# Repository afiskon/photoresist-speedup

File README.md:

# photoresist-speedup

Исходники к статье "Паяем таймер и матрицу из УФ-светодиодов для быстрой
засветки фоторезиста".

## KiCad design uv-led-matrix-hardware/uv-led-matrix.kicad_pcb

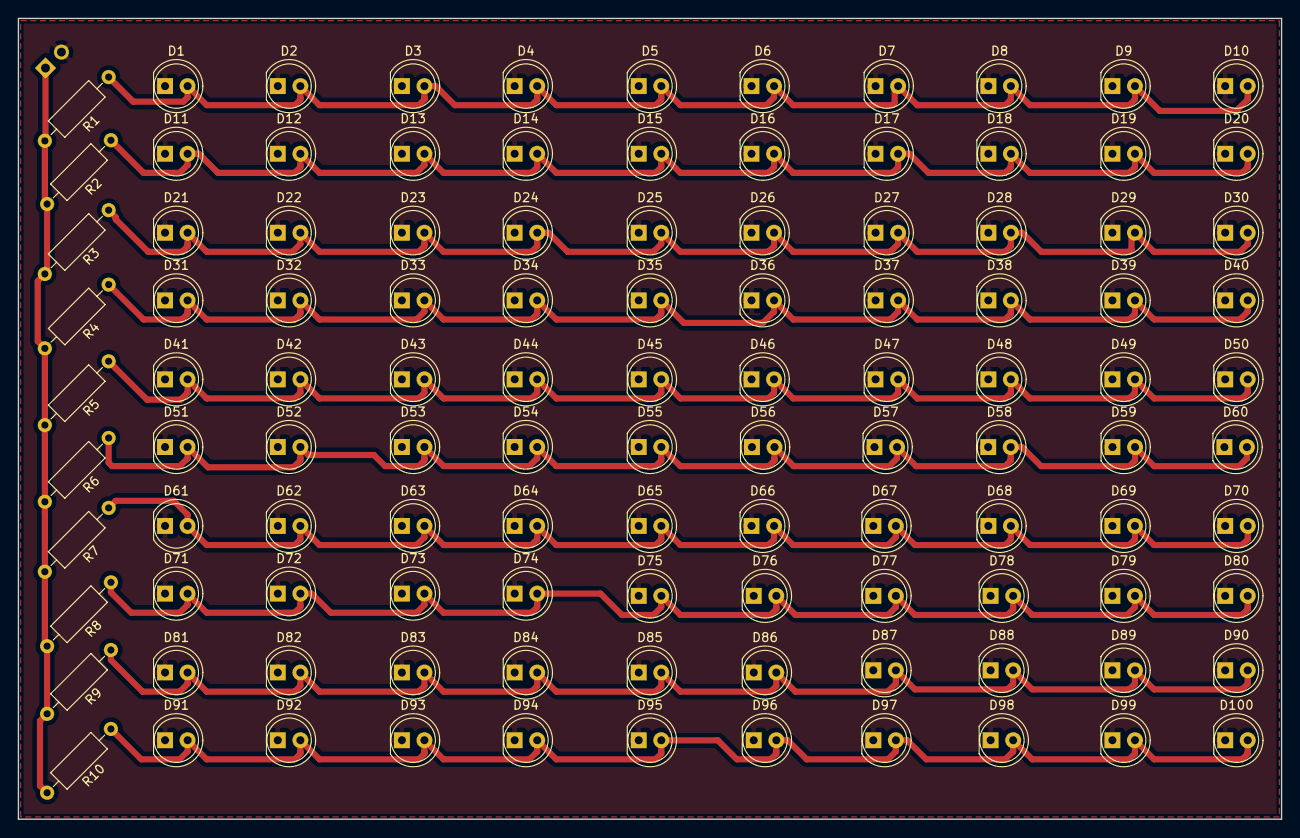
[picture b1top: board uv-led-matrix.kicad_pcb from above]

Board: 2 copper layers, 142.2 x 90.2 mm, 111 parts (1 on the bottom side), 12 nets.

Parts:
D1, D2, D3, D4, D5, D6, D7, D8, D9, D10, D11, D12, D13, D14, D15, D16, D17, D18, D19, D20, D21, D22, D23, D24, D25, D26, D27, D28, D29, D30, D31, D32, D33, D34, D35, D36, D37, D38, D39, D40, D41, D42, D43, D44, D45, D46, D47, D48, D49, D50, D51, D52, D53, D54, D55, D56, D57, D58, D59, D60, D61, D62, D63, D64, D65, D66, D67, D68, D69, D70, D71, D72, D73, D74, D75, D76, D77, D78, D79, D80, D81, D82, D83, D84, D85, D86, D87, D88, D89, D90, D91, D92, D93, D94, D95, D96, D97, D98, D99, D100: LED; LED_D5.0mm
J1: Conn_01x02; Pin_Header_Straight_1x02_Pitch2.54mm
R1, R2, R3, R4, R5, R6, R7, R8, R9, R10: 27; R_Axial_DIN0207_L6.3mm_D2.5mm_P10.16mm_Horizontal

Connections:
+5V: J1.1, R1.2, R2.2, R3.2, R4.2, R5.2, R6.2, R7.2, R8.2, R9.2, R10.2
GND: D1.1, D2.1, D3.1, D4.1, D5.1, D6.1, D7.1, D8.1, D9.1, D10.1, D11.1, D12.1, D13.1, D14.1, D15.1, D16.1, D17.1, D18.1, D19.1, D20.1, D21.1, D22.1, D23.1, D24.1, D25.1, D26.1, D27.1, D28.1, D29.1, D30.1, D31.1, D32.1, D33.1, D34.1, D35.1, D36.1, D37.1, D38.1, D39.1, D40.1, D41.1, D42.1, D43.1, D44.1, D45.1, D46.1, D47.1, D48.1, D49.1, D50.1, D51.1, D52.1, D53.1, D54.1, D55.1, D56.1, D57.1, D58.1, D59.1, D60.1, D61.1, D62.1, D63.1, D64.1, D65.1, D66.1, D67.1, D68.1, D69.1, D70.1, D71.1, D72.1, D73.1, D74.1, D75.1, D76.1, D77.1, D78.1, D79.1, D80.1, D81.1, D82.1, D83.1, D84.1, D85.1, D86.1, D87.1, D88.1, D89.1, D90.1, D91.1, D92.1, D93.1, D94.1, D95.1, D96.1, D97.1, D98.1, D99.1, D100.1, J1.2
unnamed: D1.2, D2.2, D3.2, D4.2, D5.2, D6.2, D7.2, D8.2, D9.2, D10.2, R1.1
unnamed: D11.2, D12.2, D13.2, D14.2, D15.2, D16.2, D17.2, D18.2, D19.2, D20.2, R2.1
unnamed: D21.2, D22.2, D23.2, D24.2, D25.2, D26.2, D27.2, D28.2, D29.2, D30.2, R3.1
unnamed: D31.2, D32.2, D33.2, D34.2, D35.2, D36.2, D37.2, D38.2, D39.2, D40.2, R4.1
unnamed: D41.2, D42.2, D43.2, D44.2, D45.2, D46.2, D47.2, D48.2, D49.2, D50.2, R5.1
unnamed: D51.2, D52.2, D53.2, D54.2, D55.2, D56.2, D57.2, D58.2, D59.2, D60.2, R6.1
unnamed: D61.2, D62.2, D63.2, D64.2, D65.2, D66.2, D67.2, D68.2, D69.2, D70.2, R7.1
unnamed: D71.2, D72.2, D73.2, D74.2, D75.2, D76.2, D77.2, D78.2, D79.2, D80.2, R8.1
unnamed: D81.2, D82.2, D83.2, D84.2, D85.2, D86.2, D87.2, D88.2, D89.2, D90.2, R9.1
unnamed: D91.2, D92.2, D93.2, D94.2, D95.2, D96.2, D97.2, D98.2, D99.2, D100.2, R10.1

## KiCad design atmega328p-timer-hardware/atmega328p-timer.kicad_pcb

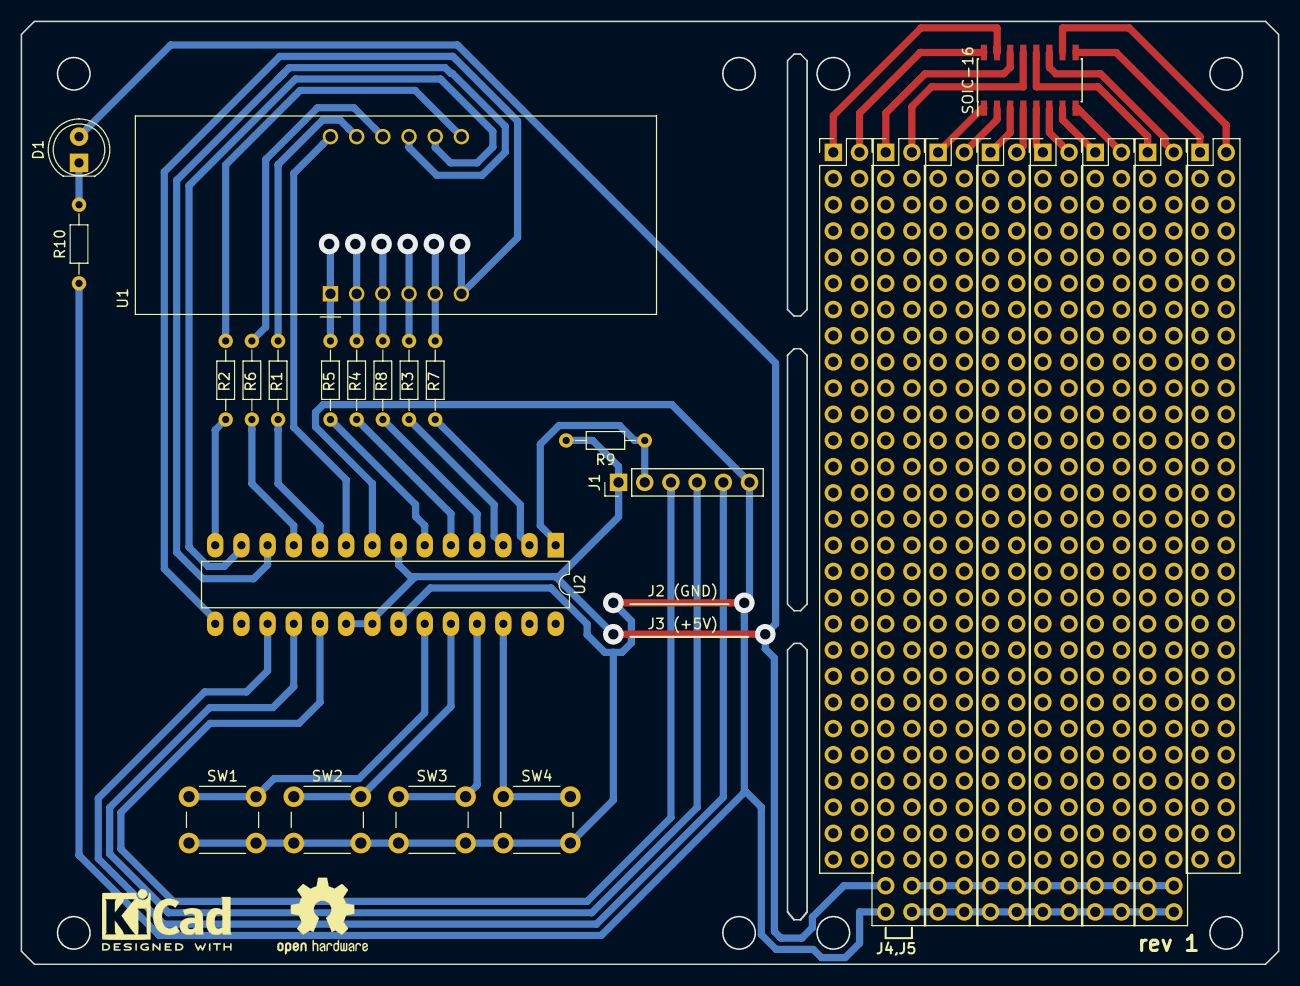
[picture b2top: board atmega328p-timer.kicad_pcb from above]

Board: 2 copper layers, 121.9 x 91.4 mm, 19 parts (0 on the bottom side), 31 nets.

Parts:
D1: LED; LED_D5.0mm
J1: Conn_01x06; Pin_Header_Straight_1x06_Pitch2.54mm
R1, R2, R3, R4, R5, R6, R7, R8, R10: 270; R_Axial_DIN0204_L3.6mm_D1.6mm_P7.62mm_Horizontal
R9: 10K; R_Axial_DIN0204_L3.6mm_D1.6mm_P7.62mm_Horizontal
SOIC-16: SOIC-16_3.9x9.9mm_Pitch1.27mm
SW1, SW2, SW3, SW4: SW_Push; SW_PUSH_6mm
U1: CA56-12CGKWA
U2: ATMEGA168A-PU; DIP-28_W7.62mm_LongPads

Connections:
+5V: D1.2, J1.1, R9.2, U2.7, U2.20, U2.21
GND: J1.6, R10.1, SW1.2, SW2.2, SW3.2, SW4.2, U2.8, U2.22
MISO: J1.4, U2.18
MOSI: J1.5, U2.17
unnamed: D1.1, R10.2
unnamed: R1.1, U1.11
unnamed: R2.1, U1.7
unnamed: R3.1, U1.4
unnamed: R4.1, U1.2
unnamed: R5.1, U1.1
unnamed: R6.1, U1.10
unnamed: R7.1, U1.5
unnamed: R8.1, U1.3
PB0: R2.2, U2.14
PB1: U1.6, U2.15
PB6: U1.12, U2.9
PB7: R1.2, U2.10
PC0: SW1.1, U2.23
PC1: SW2.1, U2.24
PC2: SW3.1, U2.25
PC3: SW4.1, U2.26
PD0: R7.2, U2.2
PD1: R3.2, U2.3
PD2: R8.2, U2.4
PD3: R4.2, U2.5
PD4: R5.2, U2.6
PD5: R6.2, U2.11
PD6: U1.9, U2.12
PD7: U1.8, U2.13
RESET: J1.2, R9.1, U2.1
SCK: J1.3, U2.19

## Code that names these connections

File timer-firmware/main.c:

/* vim: set ai et ts=4 sw=4: */

#define F_CPU 1000000

#include <avr/io.h>
#include <avr/eeprom.h>
#include <util/delay.h>
#include <string.h>
#include <stdbool.h>

void inc_time(int8_t* time) {
    for(uint8_t i = 0; i < 4; i++) {
        time[i]++;
        if(time[i] == 10) {
            // digit overflowed, go to the next one
            time[i] = 0;
        } else {
            // done!
            break;
        }
    }
}

void dec_time(int8_t* time) {
    for(uint8_t i = 0; i < 4; i++) {
        time[i]--;
        if(time[i] == -1) {
            // digit overflowed, go to the next one
            time[i] = 9;
        } else {
            // done!
            break;
        }
    }
}

bool time_is_zero(int8_t* time) {
    return (!time[0]) && (!time[1]) && (!time[2]) && (!time[3]);
}

void relay(bool on) {
    if(on) {
        PORTB |= (1 << 5);
    } else {
        PORTB &= ~(1 << 5);
    }
}

void seg_g(bool on) {
    if(on) {
        PORTD |= (1 << 0);
    } else {
        PORTD &= ~(1 << 0);
    }
}

void seg_c(bool on) {
    if(on) {
        PORTD |= (1 << 1);
    } else {
        PORTD &= ~(1 << 1);
    }
}

void seg_h(bool on) {
    if(on) {
        PORTD |= (1 << 2);
    } else {
        PORTD &= ~(1 << 2);
    }
}

void seg_d(bool on) {
    if(on) {
        PORTD |= (1 << 3);
    } else {
        PORTD &= ~(1 << 3);
    }
}

void seg_e(bool on) {
    if(on) {
        PORTD |= (1 << 4);
    } else {
        PORTD &= ~(1 << 4);
    }
}

void digit0(bool on) {
    // _low_ voltage enables the digit
    if(on) {
        PORTB &= ~(1 << 6);
    } else {
        PORTB |= (1 << 6);
    }
}

void seg_a(bool on) {
    if(on) {
        PORTB |= (1 << 7);
    } else {
        PORTB &= ~(1 << 7);
    }
}

void seg_f(bool on) {
    if(on) {
        PORTD |= (1 << 5);
    } else {
        PORTD &= ~(1 << 5);
    }
}

void digit1(bool on) {
    // _low_ voltage enables the digit
    if(on) {
        PORTD &= ~(1 << 6);
    } else {
        PORTD |= (1 << 6);
    }
}

void digit2(bool on) {
    // _low_ voltage enables the digit
    if(on) {
        PORTD &= ~(1 << 7);
    } else {
        PORTD |= (1 << 7);
    }
}

void seg_b(bool on) {
    if(on) {
        PORTB |= (1 << 0);
    } else {
        PORTB &= ~(1 << 0);
    }
}

void digit3(bool on) {
    // _low_ voltage enables the digit
    if(on) {
        PORTB &= ~(1 << 1);
    } else {
        PORTB |= (1 << 1);
    }
}

void digit(int8_t num, bool on) {
    switch(num) {
        case 0:
            digit0(on);
            break;
        case 1:
            digit1(on);
            break;
        case 2:
            digit2(on);
            break;
        case 3:
            digit3(on);
            break;
        default:
            break;
            // do nothing; should never happen
    }
}

inline bool inc_pressed() {
    // the button is pulled-up to VCC, the button is conneted to GND
    // i.e. low voltage means that the button is pressed
    return !(PINC & (1 << 0));
}

inline bool dec_pressed() {
    // the button is pulled-up to VCC, the button is conneted to GND
    // i.e. low voltage means that the button is pressed
    return !(PINC & (1 << 1));
}

inline bool start_pressed() {
    // the button is pulled-up to VCC, the button is conneted to GND
    // i.e. low voltage means that the button is pressed
    return !(PINC & (1 << 2));
}

inline bool save_pressed() {
    // the button is pulled-up to VCC, the button is conneted to GND
    // i.e. low voltage means that the button is pressed
    return !(PINC & (1 << 3));
}

void encode_digit(int8_t d) {
    seg_a(d == 0 || d == 2 || d == 3 || ((d >= 5) && (d <= 9)));
    seg_b(((d >= 0) && (d <= 4)) || ((d >= 7) && (d <= 9)));
    seg_c(d == 0 || d == 1 || d == 3 || ((d >= 4) && (d <= 9)));
    seg_d(d == 0 || d == 2 || d == 3 || d == 5 || d == 6 || d == 8 || d == 9);
    seg_e(d == 0 || d == 2 || d == 6 || d == 8);
    seg_f(d == 0 || ((d >= 4) && (d <= 6)) || d == 8 || d == 9);
    seg_g(d == 2 || d == 3 || ((d >= 4) && (d <= 6)) || d == 8 || d == 9);
}


int8_t saved_timeout[4] EEMEM = {0, 2, 0, 0}; // 20 seconds
int8_t timeout[4];
int8_t countdown[4];
uint16_t countdown_ms;
bool countdown_active = false;
bool inc_was_released = true;
bool dec_was_released = true;
bool start_was_released = true;
bool save_was_released = true;

void setup() {
    // load timeout from the EEPROM
    eeprom_read_block(timeout, saved_timeout, sizeof(timeout));

    DDRB = 0;
    // PB5 = relay control
    DDRB |= (1 << 5);
    relay(false);
    // PB0, PB1, PB6 and PB7 are used to drive LED indicator
    DDRB |= (1 << 0) | (1 << 1) | (1 << 6) | (1 << 7);
    //PD0-PD8 are used to drive LED indicator as well
    DDRD = 0xFF; 

    DDRC = 0; // PC0-PC3 = buttons
    PORTC = 0xFF; // enable pull-up resistors

    // initially none of the numbers is chosen
    digit0(false);
    digit1(false);
    digit2(false);
    digit3(false);
}

void loop() {
    bool old_countdown_active = countdown_active;
    
    for(int8_t i = 0; i < 4; i++) {
        encode_digit(countdown_active ? countdown[3-i] : timeout[3-i]);
        digit(i, true);
        _delay_ms(5);
        countdown_ms += countdown_active ? 5 : 0;
        digit(i, false);
    }

    if(!countdown_active && inc_pressed()) {
        if(inc_was_released) { // debounce
            inc_time(timeout);
            inc_was_released = false;
        }
    } else
        inc_was_released = true;

    if(!countdown_active && dec_pressed()) {
        if(dec_was_released) { // debounce
            dec_time(timeout);
            dec_was_released = false;
        }
    } else
        dec_was_released = true;

    if(!countdown_active && save_pressed()) {
        if(save_was_released) { // debounce
            // save current timeout to the EEPROM
            eeprom_update_block(timeout, saved_timeout, sizeof(timeout));
            save_was_released = false;
        }
    } else
        save_was_released = true;

    if(start_pressed()) {
        if(start_was_released) { // debounce
            if(countdown_active) {
                // stop the countdown
                countdown_active = false;
            } else {
                if(!time_is_zero(timeout)) {
                    // start the countdown
                    memcpy(countdown, timeout, sizeof(timeout));
                    countdown_ms = 0;
                    countdown_active = true;
                }
            }
            start_was_released = false;
        }
    } else
        start_was_released = true;

    if(countdown_active && (countdown_ms >= 1000)) {
        // one second has passed
        dec_time(countdown);
        countdown_ms -= 1000;
        if(time_is_zero(countdown)) {
            // stop the countdown
            countdown_active = false;
        }
    }

    if(old_countdown_active != countdown_active) {
        // change the port state only if necessary
        relay(countdown_active);
    }
}

int main() {
    setup();
    while(1) {
        loop();
    }
    return 0;
}

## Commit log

2018-02-03 Timer firmware moved from a sandbox repository
2018-02-03 Timer KiCad files moved from a sandbox repository
2018-02-03 gerber.zip
2018-02-03 UV LED matrix KiCad files moved from a sandbox repository
2018-02-03 Create firmware/ and hardware/ directories
2018-02-03 Time-test PCB KiCad files moved from a sandbox repository
